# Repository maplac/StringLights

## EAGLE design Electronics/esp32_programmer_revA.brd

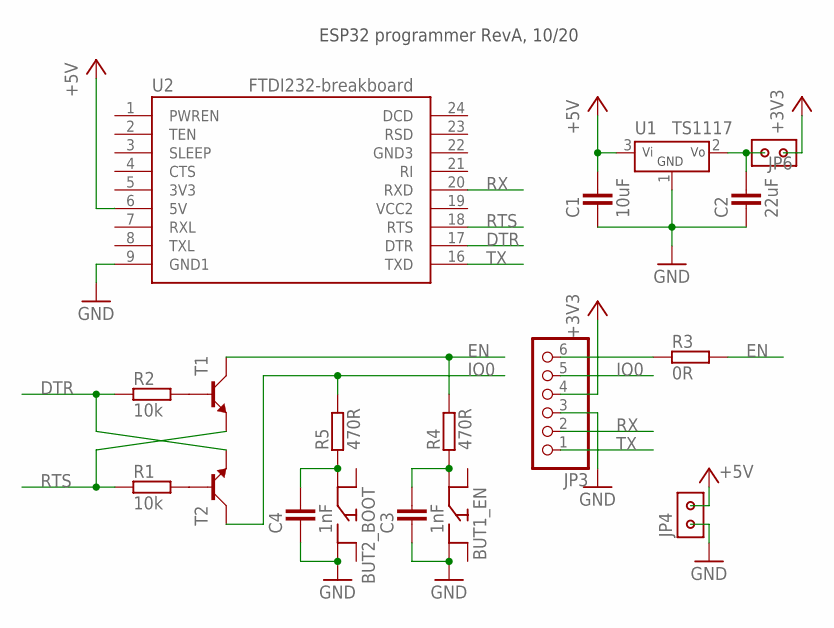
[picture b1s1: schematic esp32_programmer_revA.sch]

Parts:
BUT1_EN, BUT2_BOOT: BUTTON'SMD'; BUTTON_SMD
C1: 10uF; C0805
C2: 22uF; C0805
C3, C4: 1nF; C0805
JP3: PINHD-1X6; 1X06
JP4, JP6: PINHD-2X1
R1, R2: 10k; R0805
R3: 0R; R0805
R4, R5: 470R; R0805
T1, T2: TRAN_NPN'BC817'; SOT23
U1: TS1117; SOT223
U2: FTDI232-BREAKBOARD-SIMPLE; FTDI232-BRAKBOARD-SIMPLE

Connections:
3V3: U2.5 (3V3)
+3V3: JP3.4, JP6.2
+5V: C1.2, JP4.1, U1.3 (VIN), U2.6 (5V)
DTR: R2.1, T2.2 (E), U2.17 (DTR)
EN: R3.2, R4.2, T1.3 (C)
GND: BUT1_EN.3 (1), BUT2_BOOT.3 (1), C1.1, C2.1, C3.1, C4.1, JP3.3, JP4.2, U1.1 (GND), U2.9 (GND1)
GND3: U2.22 (GND3)
IO0: JP3.5, R5.2, T2.3 (C)
unnamed: R2.2, T1.1 (B)
unnamed: R1.2, T2.1 (B)
unnamed: BUT1_EN.2, C3.2, R4.1
unnamed: JP3.6, R3.1
unnamed: BUT2_BOOT.2, C4.2, R5.1
unnamed: C2.2, JP6.1, U1.2 (VOUT)
RTS: R1.1, T1.2 (E), U2.18 (RTS)
RX: JP3.2, U2.20 (RXD)
TX: JP3.1, U2.16 (TXD)
VCC2: U2.19 (VCC2)

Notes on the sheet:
ESP32 programmer RevA, 10/20

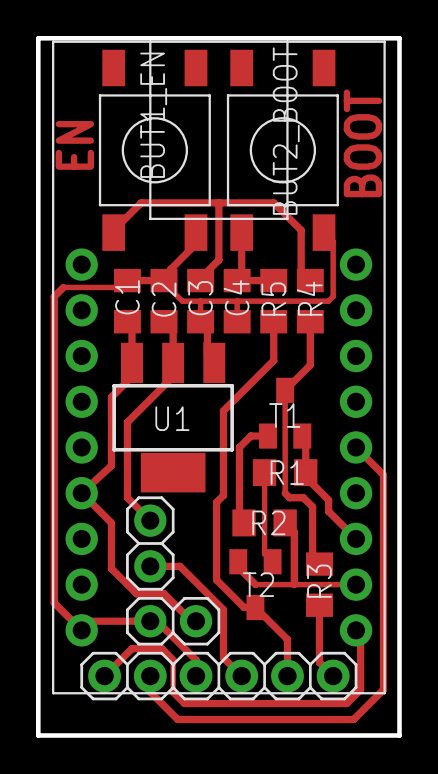
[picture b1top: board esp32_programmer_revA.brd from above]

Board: 2 copper layers, 20.1 x 38.7 mm, 18 parts (0 on the bottom side), 15 nets.

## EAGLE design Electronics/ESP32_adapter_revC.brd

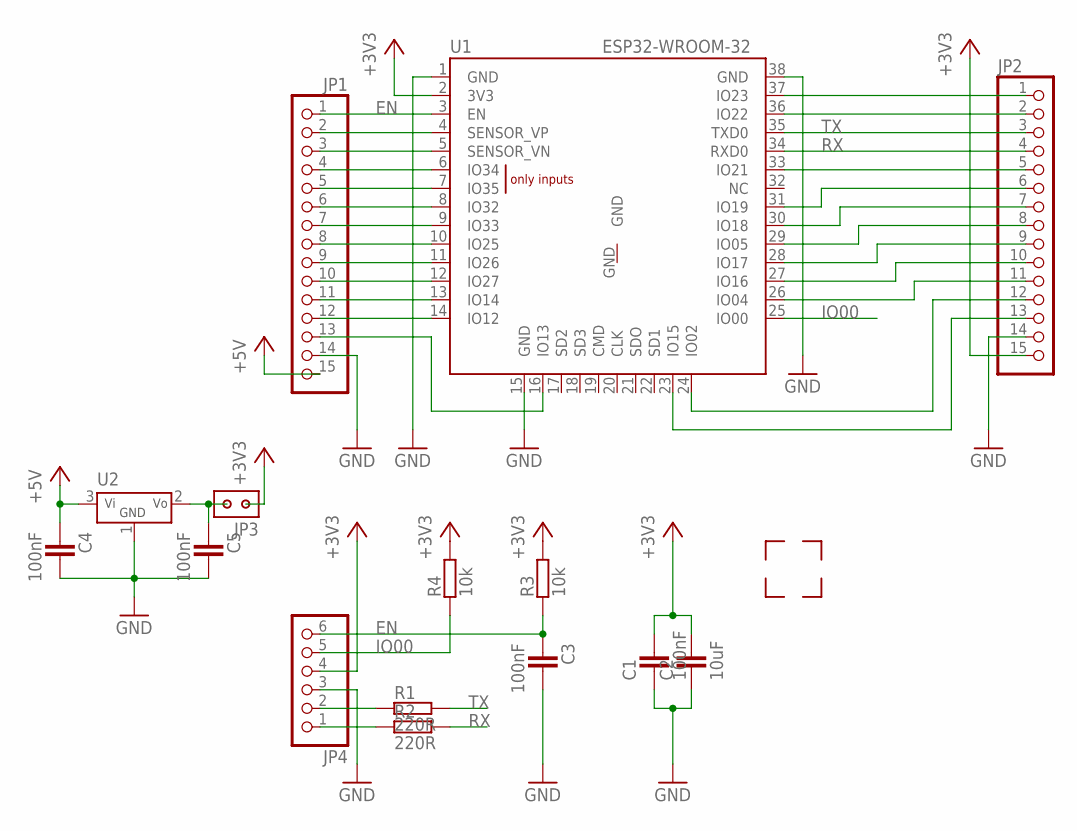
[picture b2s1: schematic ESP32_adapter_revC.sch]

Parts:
C1, C3, C4, C5: 100nF; C0805
C2: 10uF; C0805
JP1, JP2: PINHD-1X15; 1X15
JP3: PINHD-2X1
JP4: PINHD-1X6; 1X06
R1, R2: 220R; R0805
R3, R4: 10k; R0805
U1: ESP-WROOM-32
U2: V_STAB'TS1117'; SOT223
U$1, U$2, U$3, U$4: CORNER

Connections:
+3V3: C1.2, C2.2, JP2.15, JP3.2, JP4.4, R3.2, R4.2, U1.2 (3V3)
+5V: C4.1, JP1.15, U2.3 (VIN)
EN: C3.1, JP1.1, JP4.6, R3.1, U1.3 (EN)
GND: C1.1, C2.1, C3.2, C4.2, C5.2, JP1.14, JP2.14, JP4.3, U1.1 (GND), U1.15 (GND), U1.38 (GND), U2.1 (GND)
IO00: JP4.5, R4.1, U1.25 (IO00)
unnamed: JP4.1, R2.1
unnamed: JP4.2, R1.1
unnamed: JP1.2, U1.4 (SENSOR_VP)
unnamed: JP1.3, U1.5 (SENSOR_VN)
unnamed: JP1.4, U1.6 (IO34)
unnamed: JP1.5, U1.7 (IO35)
unnamed: JP1.6, U1.8 (IO32)
unnamed: JP1.7, U1.9 (IO33)
unnamed: JP1.8, U1.10 (IO25)
unnamed: JP1.9, U1.11 (IO26)
unnamed: JP1.10, U1.12 (IO27)
unnamed: JP1.11, U1.13 (IO14)
unnamed: JP1.12, U1.14 (IO12)
unnamed: C5.1, JP3.1, U2.2 (VOUT)
unnamed: JP2.1, U1.37 (IO23)
unnamed: JP2.2, U1.36 (IO22)
unnamed: JP2.5, U1.33 (IO21)
unnamed: JP2.6, U1.31 (IO19)
unnamed: JP2.7, U1.30 (IO18)
unnamed: JP2.8, U1.29 (IO05)
unnamed: JP2.9, U1.28 (IO17)
unnamed: JP2.10, U1.27 (IO16)
unnamed: JP2.11, U1.26 (IO04)
unnamed: JP2.12, U1.24 (IO02)
unnamed: JP2.13, U1.23 (IO15)
unnamed: JP1.13, U1.16 (IO13)
RX: JP2.4, R2.2, U1.34 (RXD0)
TX: JP2.3, R1.2, U1.35 (TXD0)

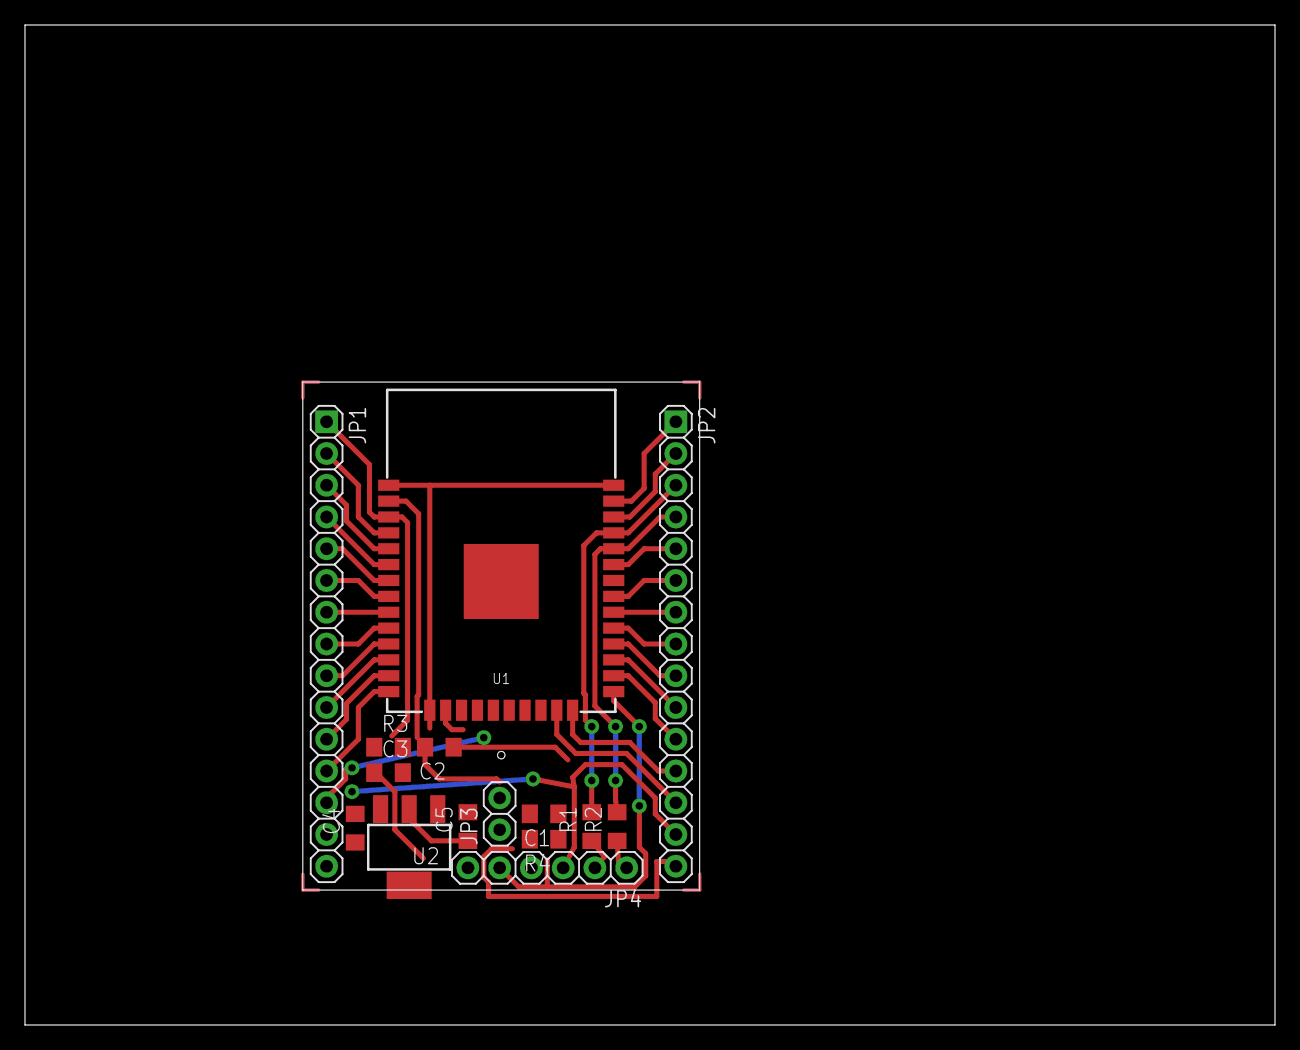
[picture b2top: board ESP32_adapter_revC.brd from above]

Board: 2 copper layers, 100.0 x 80.0 mm, 19 parts (0 on the bottom side), 33 nets.

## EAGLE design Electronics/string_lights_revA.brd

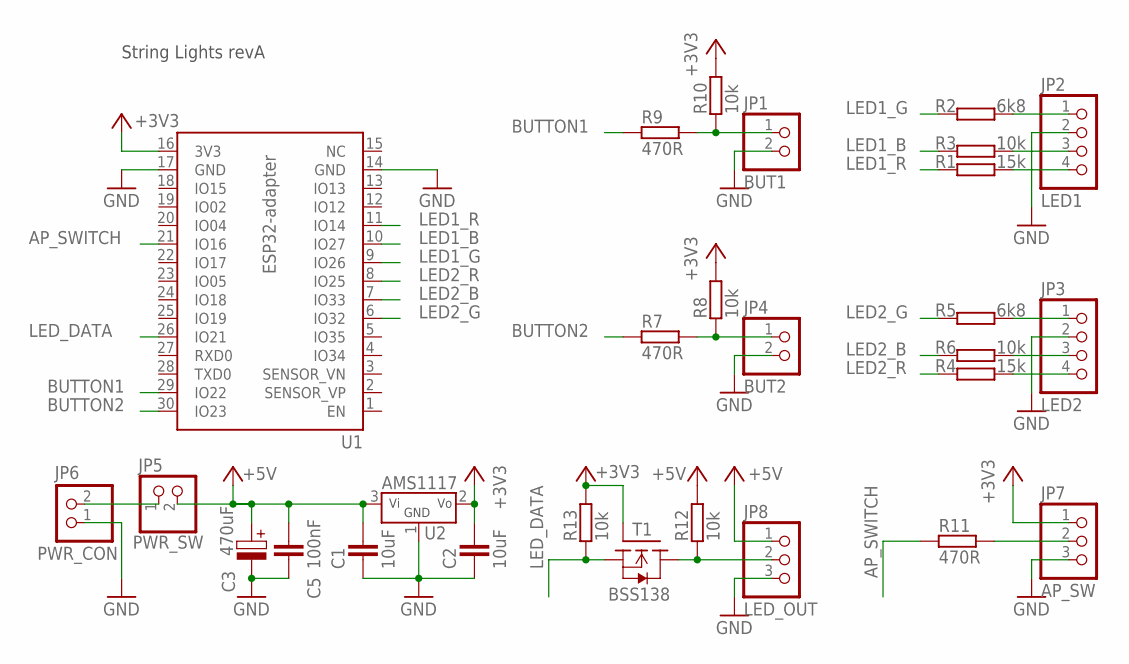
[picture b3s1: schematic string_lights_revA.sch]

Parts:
C1, C2: 10uF; C0805
C3: 470uF; ELYT-10MM
C5: 100nF; C0805
JP1: BUT1; 1X02/90
JP2: LED1; 1X04/90
JP3: LED2; 1X04/90
JP4: BUT2; 1X02/90
JP5: PWR_SW; 1X02/90
JP6: PWR_CON; 1X02/90
JP7: AP_SW; 1X03/90
JP8: LED_OUT; 1X03/90
R1, R4: 15k; R0805
R2, R5: 6k8; R0805
R3, R6, R8, R10, R12, R13: 10k; R0805
R7, R9, R11: 470R; R0805
T1: BSS138; SOT23
U1: ESP32-ADAPTER
U2: AMS1117; SOT223

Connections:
+3V3: C2.2, JP7.1, R8.2, R10.2, R13.2, T1.1 (G), U1.16 (3V3), U2.2 (VOUT)
+5V: C1.2, C3.P (POS), C5.2, JP5.2, JP8.1, R12.2, U2.3 (VIN)
AP_SWITCH: R11.1, U1.21 (IO16)
BUTTON1: R9.1, U1.29 (IO22)
BUTTON2: R7.1, U1.30 (IO23)
GND: C1.1, C2.1, C3.N (NEG), C5.1, JP1.2, JP2.2, JP3.2, JP4.2, JP6.1, JP7.3, JP8.3, U1.14 (GND), U1.17 (GND), U2.1 (GND)
LED1_B: R3.1, U1.10 (IO27)
LED1_G: R2.1, U1.9 (IO26)
LED1_R: R1.1, U1.11 (IO14)
LED2_B: R6.1, U1.7 (IO33)
LED2_G: R5.1, U1.6 (IO32)
LED2_R: R4.1, U1.8 (IO25)
LED_DATA: R13.1, T1.2 (S), U1.26 (IO21)
unnamed: JP5.1, JP6.2
unnamed: JP2.4, R1.2
unnamed: JP2.3, R3.2
unnamed: JP2.1, R2.2
unnamed: JP3.1, R5.2
unnamed: JP3.3, R6.2
unnamed: JP3.4, R4.2
unnamed: JP4.1, R7.2, R8.1
unnamed: JP1.1, R9.2, R10.1
unnamed: JP7.2, R11.2
unnamed: JP8.2, R12.1, T1.3 (D)

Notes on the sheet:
String Lights revA

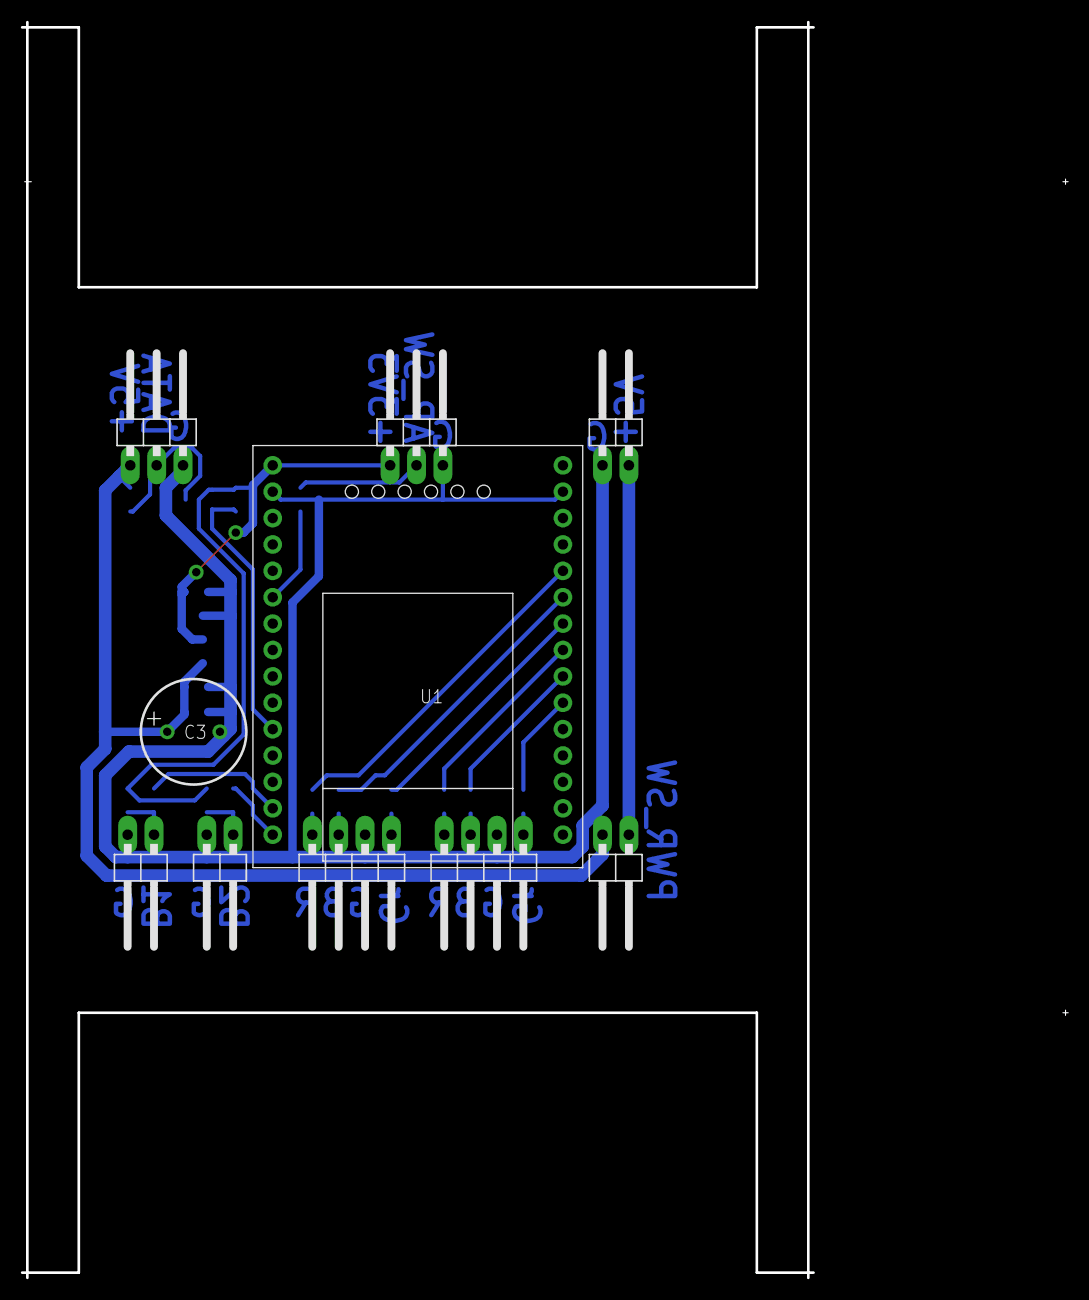
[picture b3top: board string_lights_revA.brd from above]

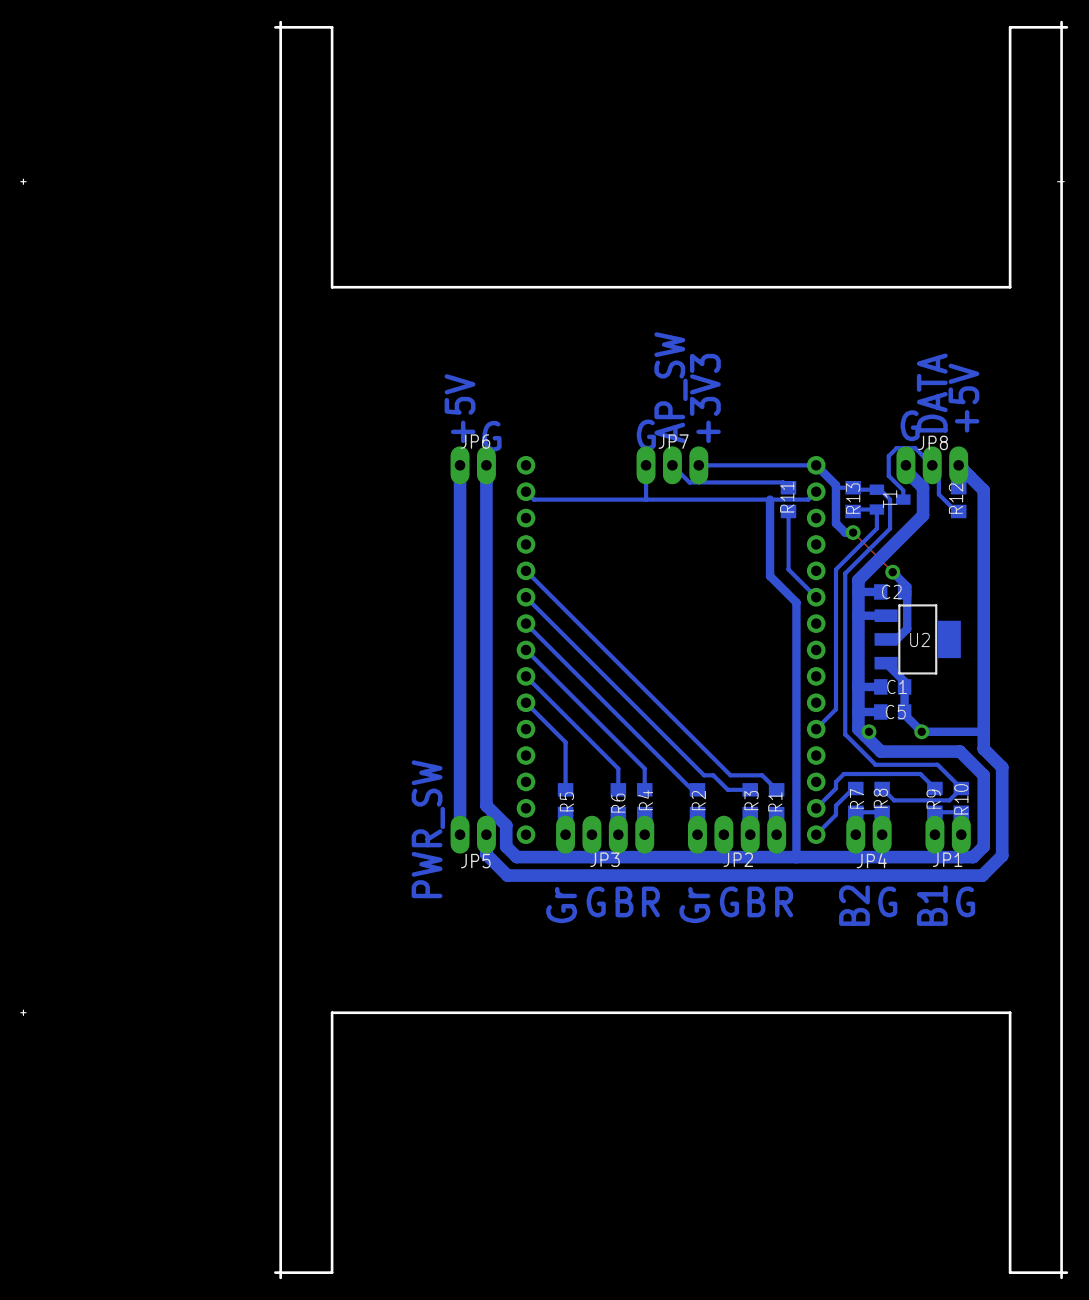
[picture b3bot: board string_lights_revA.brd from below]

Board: 2 copper layers, 100.6 x 120.9 mm, 28 parts (18 on the bottom side), 24 nets.

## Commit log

2018-12-28 added: Node.js web server for testing
2018-12-28 changed: color picker in left menu
2019-01-06 added: Single Color page
2019-01-13 changed: single color page
2019-01-20 changed: color picker variables merged into one object
2019-01-20 added: firmware for ESP8266 (Arduino IDE)
2019-01-26 added: saving and loading colors
2019-02-08 fixed: loading settings from memory
2019-02-10 added: Multi Color page
2019-02-17 changed: multi color page
2019-02-20 modified: multi color page - custom checkbox
2019-02-21 modified: multi color page - buttons for number input
2019-02-22 modified: multi color page - sending settings
2019-02-23 modified: multi color page - post data
2019-02-24 Firmware: added multi color
2019-03-01 Firwmare: saving current settings to a file
2019-03-03 single/multi color page: text shows rgb values if the name is unknown
2019-03-10 multi color page: added option to save multiple color variations
2019-03-10 Firmware: saving/loding color variations for multi color page
2019-04-14 Firmware: removed content of the data folder
2019-04-14 Added todo list.
2019-04-14 Firmware: arduino project splitted into multiple tabs
2019-04-14 Index page: added settings form.
2019-04-19 Index page: modified parameters
2019-04-19 Firmware: working with system settings
2019-04-22 Index page: added static IP settings
2019-04-22 Firmware: added static IP option
2019-04-24 Firmware: added LEDs
2019-05-04 Firmware: added HW buttons
2019-05-04 Firmware: better logging at start
2019-05-04 Firmware: fixed sending OK message when error happens
2019-05-05 Firmware: fixed turning on/off the LED strip
2019-05-05 Firmware: added transparent mode for controling the rbg LEDs without saving to memory
2019-05-05 Firmware: fixed displaying last IP address
2019-05-05 Firmware: added Access Point mode
2019-09-29 Firmware: switched to ESP32
2019-11-10 Electronics: added revA
2019-12-03 Electronics: finished RevA
2019-12-03 Electronics: documentation for RevA
2019-12-03 Electronics: added ESP32 adapter
2019-12-03 Electronics: added ESP32 programmer
2019-12-03 Firmware: various changes to make it work
2019-12-06 Firmware: multicolor has option to spread colors onto the whole led string
2019-12-11 Firmware: added actions for buttons
2019-12-14 Firmware: changed single color
2019-12-15 Firmware: changing multi color with HW button skips black slots
2019-12-15 Firmware: connecting to WiFi moved from setup to loop
2019-12-22 Electronics: added servis connector to the back panel
2019-12-22 Firmware: fixed WiFi soft AP
2019-12-22 Firmware: fixed change of color when multi color page is opened
